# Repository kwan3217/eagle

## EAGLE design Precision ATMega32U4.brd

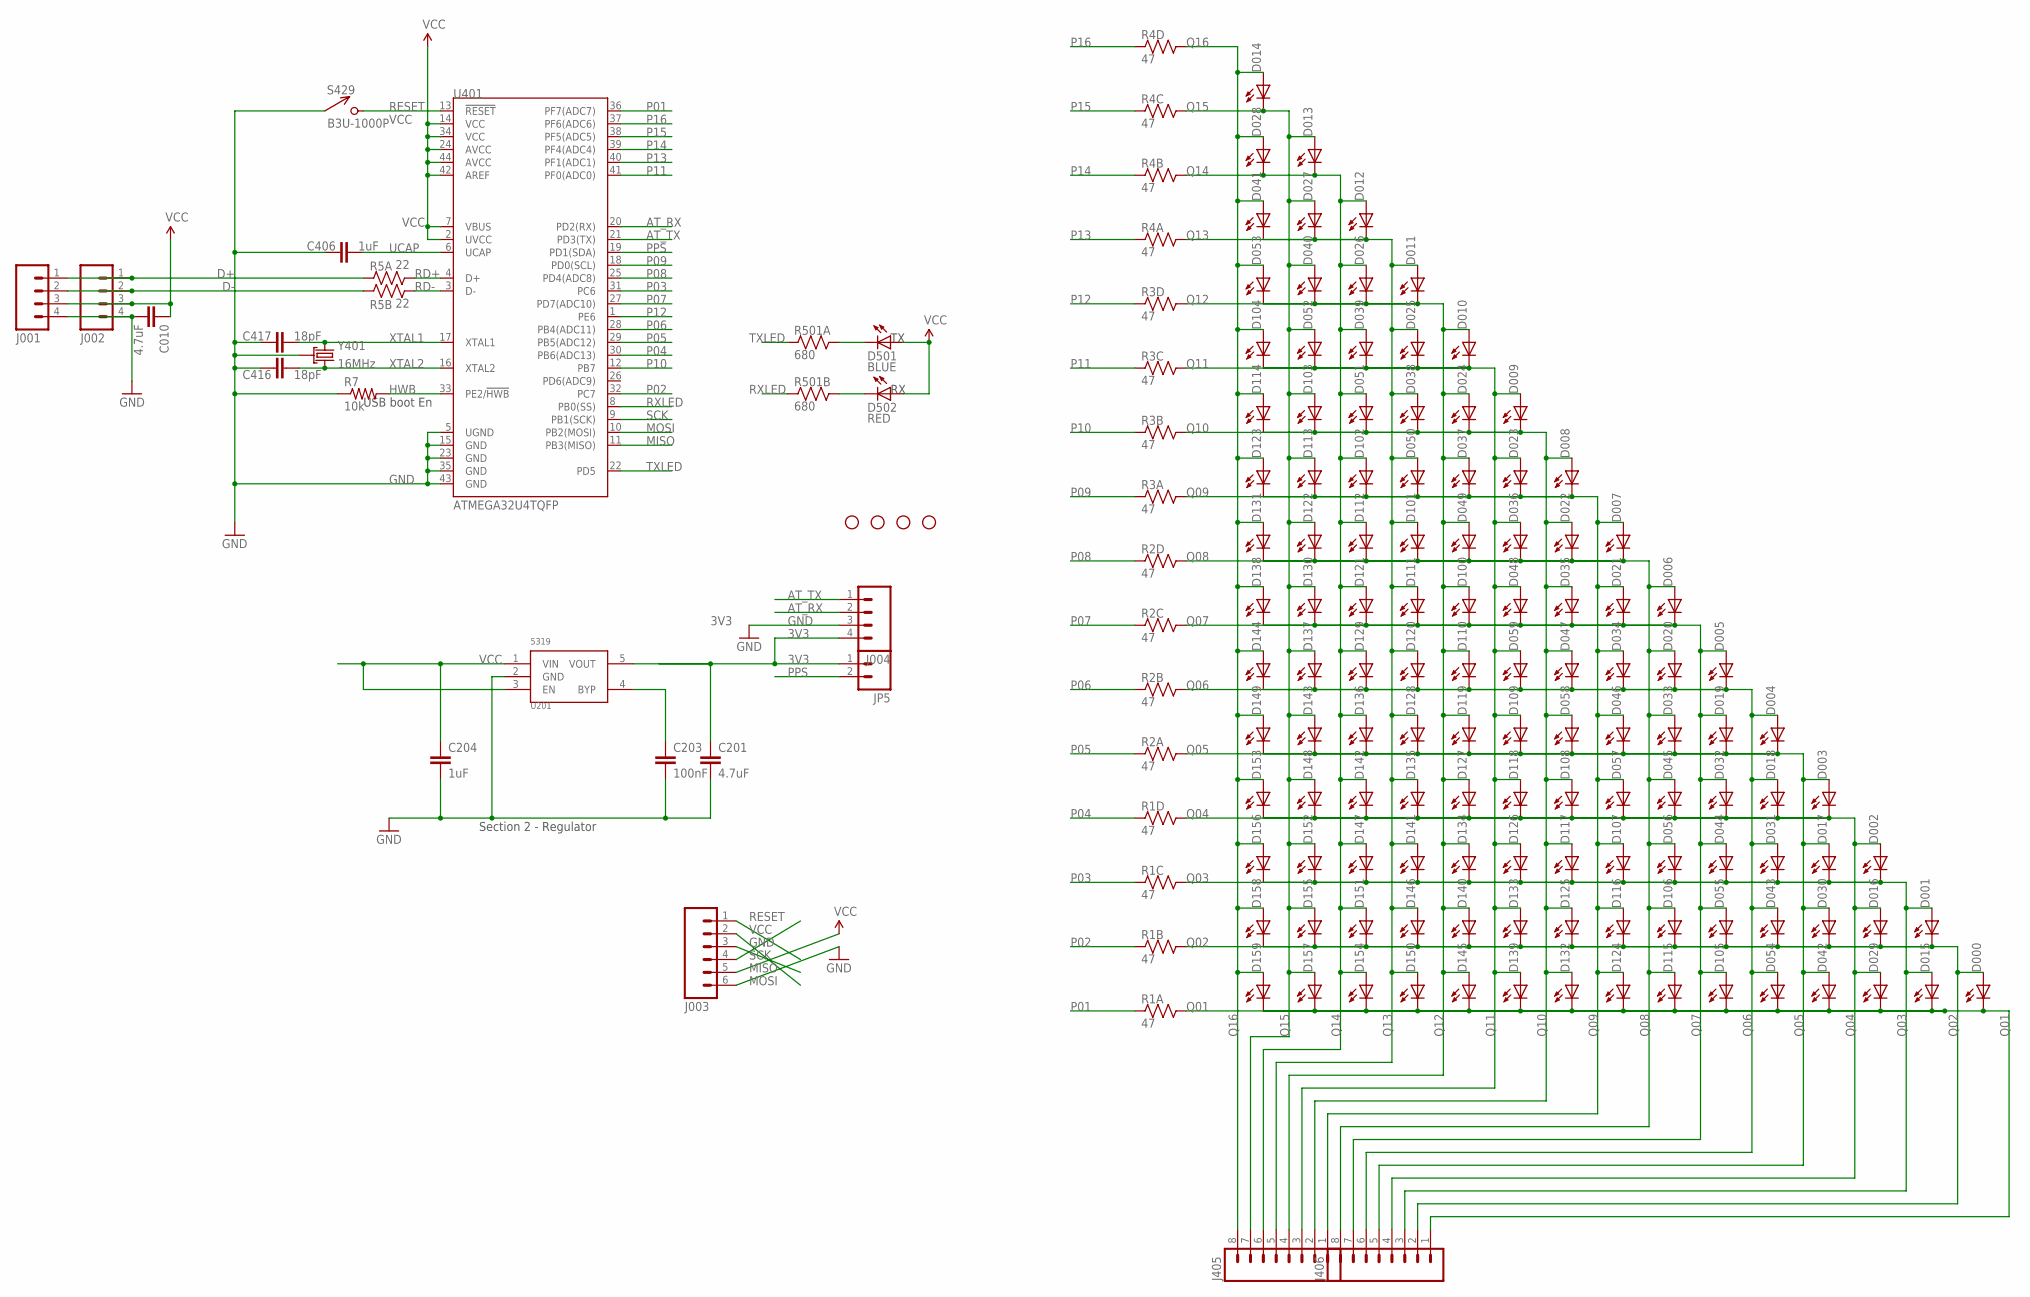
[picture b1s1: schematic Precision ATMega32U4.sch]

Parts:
C010: 4.7uF; 0603-CAP
C201: 4.7uF; 0402-CAP
C203: 100nF; 0402-CAP
C204: 1uF; 0402-CAP
C406: 1uF; 0603-CAP
C416, C417: 18pF; 0603-CAP
D000, D001, D002, D003, D004, D005, D006, D007, D008, D009, D010, D011, D012, D013, D014, D015, D016, D017, D018, D019, D020, D021, D022, D023, D024, D025, D026, D027, D028, D029, D030, D031, D032, D033, D034, D035, D036, D037, D038, D039, D040, D041, D042, D043, D044, D045, D046, D047, D048, D049, D050, D051, D052, D053, D054, D055, D056, D057, D058, D059, D100, D101, D102, D103, D104, D105, D106, D107, D108, D109, D110, D111, D112, D113, D114, D115, D116, D117, D118, D119, D120, D121, D122, D123, D124, D125, D126, D127, D128, D129, D130, D131, D132, D133, D134, D135, D136, D137, D138, D139, D140, D141, D142, D143, D144, D145, D146, D147, D148, D149, D150, D151, D152, D153, D154, D155, D156, D157, D158, D159: HOUR; LED-0603
D501: BLUE; LED-0603
D502: RED; LED-0603
J001, J002, J004: M04PTH; 1X04
J003: M06SIP; 1X06
J405, J406: M081X08; 1X08
JP1, JP2, JP3, JP4: STAND-OFF
JP5: M02PTH; 1X02
R1, R2, R3, R4: 47; CRA04
R5: 22; CRA02
R7: 10k; 0603-RES
R501: 680; CRA02
S429: B3U-1000P
U201: 5319; SOT-23-5
U401: ATMEGA32U4TQFP; SPARKFUN-DIGITALIC_TQFP44
Y401: 16MHz; CRYSTAL_SMD

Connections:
3V3: C201.1, J004.4, JP5.1, U201.5 (VOUT)
AT_RX: J004.2, U401.20 (PD2(RX))
AT_TX: J004.1, U401.21 (PD3(TX))
D+: J001.1, J002.1, R5.1
D-: J001.2, J002.2, R5.2 (1)
GND: C010.2, C201.2, C203.2, C204.2, C406.2, C416.1, C417.1, J001.4, J002.4, J003.6, J004.3, R7.1, S429.P$1 (1), U201.2 (GND), U401.5 (UGND), U401.15 (GND), U401.23 (GND), U401.35 (GND), U401.43 (GND), Y401.2 (GND), Y401.4 (GND)
HWB: R7.2, U401.33 (PE2/!HWB)
MISO: J003.3, U401.11 (PB3(MISO))
MOSI: J003.2, U401.10 (PB2(MOSI))
unnamed: C203.1, U201.4 (BYP)
P01: R1.1, U401.36 (PF7(ADC7))
P02: R1.2 (1), U401.32 (PC7)
P03: R1.3 (1), U401.31 (PC6)
P04: R1.4 (1), U401.30 (PB6(ADC13))
P05: R2.1, U401.29 (PB5(ADC12))
P06: R2.2 (1), U401.28 (PB4(ADC11))
P07: R2.3 (1), U401.27 (PD7(ADC10))
P08: R2.4 (1), U401.25 (PD4(ADC8))
P09: R3.1, U401.18 (PD0(SCL))
P10: R3.2 (1), U401.12 (PB7)
P11: R3.3 (1), U401.41 (PF0(ADC0))
P12: R3.4 (1), U401.1 (PE6)
P13: R4.1, U401.40 (PF1(ADC1))
P14: R4.2 (1), U401.39 (PF4(ADC4))
P15: R4.3 (1), U401.38 (PF5(ADC5))
P16: R4.4 (1), U401.37 (PF6(ADC6))
PPS: JP5.2, U401.19 (PD1(SDA))
Q01: D000.C, D015.C, D029.C, D042.C, D054.C, D105.C, D115.C, D124.C, D132.C, D139.C, D145.C, D150.C, D154.C, D157.C, D159.C, J406.1, R1.8 (2)
Q02: D000.A, D001.C, D016.C, D030.C, D043.C, D055.C, D106.C, D116.C, D125.C, D133.C, D140.C, D146.C, D151.C, D155.C, D158.C, J406.2, R1.7 (2)
Q03: D001.A, D002.C, D015.A, D017.C, D031.C, D044.C, D056.C, D107.C, D117.C, D126.C, D134.C, D141.C, D147.C, D152.C, D156.C, J406.3, R1.6 (2)
Q04: D002.A, D003.C, D016.A, D018.C, D029.A, D032.C, D045.C, D057.C, D108.C, D118.C, D127.C, D135.C, D142.C, D148.C, D153.C, J406.4, R1.5 (2)
Q05: D003.A, D004.C, D017.A, D019.C, D030.A, D033.C, D042.A, D046.C, D058.C, D109.C, D119.C, D128.C, D136.C, D143.C, D149.C, J406.5, R2.8 (2)
Q06: D004.A, D005.C, D018.A, D020.C, D031.A, D034.C, D043.A, D047.C, D054.A, D059.C, D110.C, D120.C, D129.C, D137.C, D144.C, J406.6, R2.7 (2)
Q07: D005.A, D006.C, D019.A, D021.C, D032.A, D035.C, D044.A, D048.C, D055.A, D100.C, D105.A, D111.C, D121.C, D130.C, D138.C, J406.7, R2.6 (2)
Q08: D006.A, D007.C, D020.A, D022.C, D033.A, D036.C, D045.A, D049.C, D056.A, D101.C, D106.A, D112.C, D115.A, D122.C, D131.C, J406.8, R2.5 (2)
Q09: D007.A, D008.C, D021.A, D023.C, D034.A, D037.C, D046.A, D050.C, D057.A, D102.C, D107.A, D113.C, D116.A, D123.C, D124.A, J405.1, R3.8 (2)
Q10: D008.A, D009.C, D022.A, D024.C, D035.A, D038.C, D047.A, D051.C, D058.A, D103.C, D108.A, D114.C, D117.A, D125.A, D132.A, J405.2, R3.7 (2)
Q11: D009.A, D010.C, D023.A, D025.C, D036.A, D039.C, D048.A, D052.C, D059.A, D104.C, D109.A, D118.A, D126.A, D133.A, D139.A, J405.3, R3.6 (2)
Q12: D010.A, D011.C, D024.A, D026.C, D037.A, D040.C, D049.A, D053.C, D100.A, D110.A, D119.A, D127.A, D134.A, D140.A, D145.A, J405.4, R3.5 (2)
Q13: D011.A, D012.C, D025.A, D027.C, D038.A, D041.C, D050.A, D101.A, D111.A, D120.A, D128.A, D135.A, D141.A, D146.A, D150.A, J405.5, R4.8 (2)
Q14: D012.A, D013.C, D026.A, D028.C, D039.A, D051.A, D102.A, D112.A, D121.A, D129.A, D136.A, D142.A, D147.A, D151.A, D154.A, J405.6, R4.7 (2)
Q15: D013.A, D014.C, D027.A, D040.A, D052.A, D103.A, D113.A, D122.A, D130.A, D137.A, D143.A, D148.A, D152.A, D155.A, D157.A, J405.7, R4.6 (2)
Q16: D014.A, D028.A, D041.A, D053.A, D104.A, D114.A, D123.A, D131.A, D138.A, D144.A, D149.A, D153.A, D156.A, D158.A, D159.A, J405.8, R4.5 (2)
RD+: R5.4 (2), U401.4 (D+)
RD-: R5.3 (2), U401.3 (D-)
RESET: J003.4, S429.P$2 (2), U401.13 (!RESET)
RXLED: R501.2 (1), U401.8 (PB0(SS))
RXLED+: D502.C, R501.3 (2)
SCK: J003.1, U401.9 (PB1(SCK))
TXLED: R501.1, U401.22 (PD5)
TXLED+: D501.C, R501.4 (2)
UCAP: C406.1, U401.6 (UCAP)
VCC: C010.1, C204.1, D501.A, D502.A, J001.3, J002.3, J003.5, U201.1 (VIN), U201.3 (EN), U401.2 (UVCC), U401.7 (VBUS), U401.14 (VCC), U401.24 (AVCC), U401.34 (VCC), U401.42 (AREF), U401.44 (AVCC)
XTAL1: C417.2, U401.17 (XTAL1), Y401.1
XTAL2: C416.2, U401.16 (XTAL2), Y401.3 (2)

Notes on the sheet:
USB boot En
Section 2 - Regulator

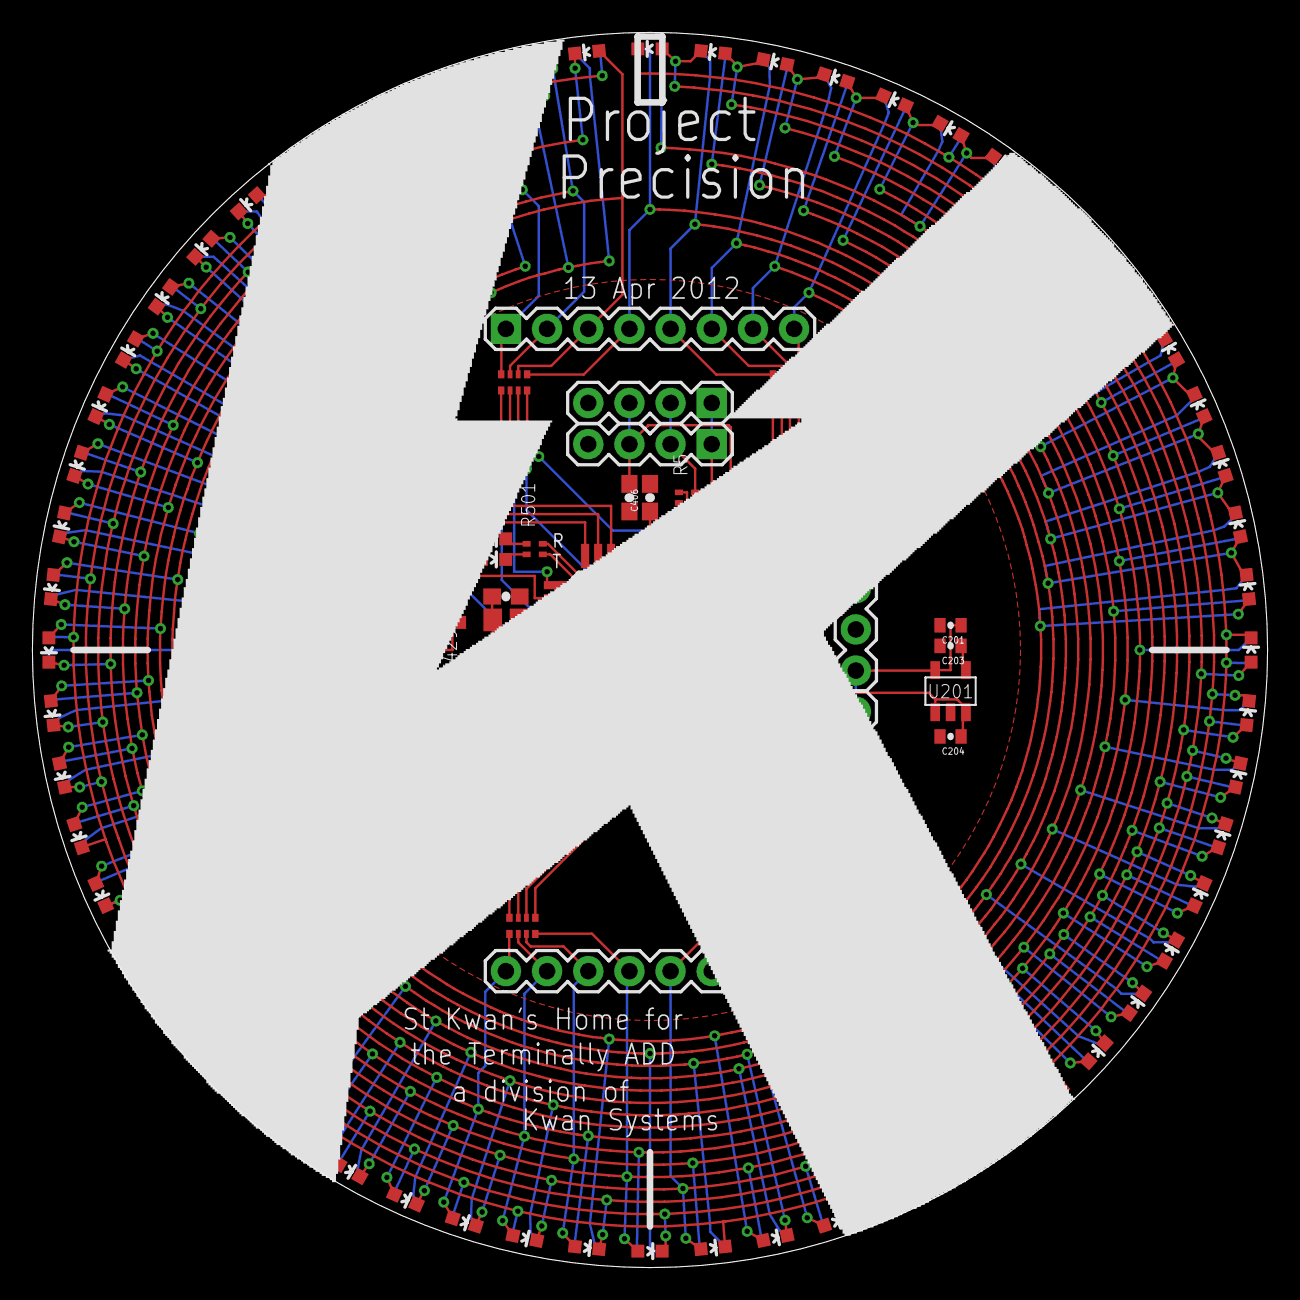
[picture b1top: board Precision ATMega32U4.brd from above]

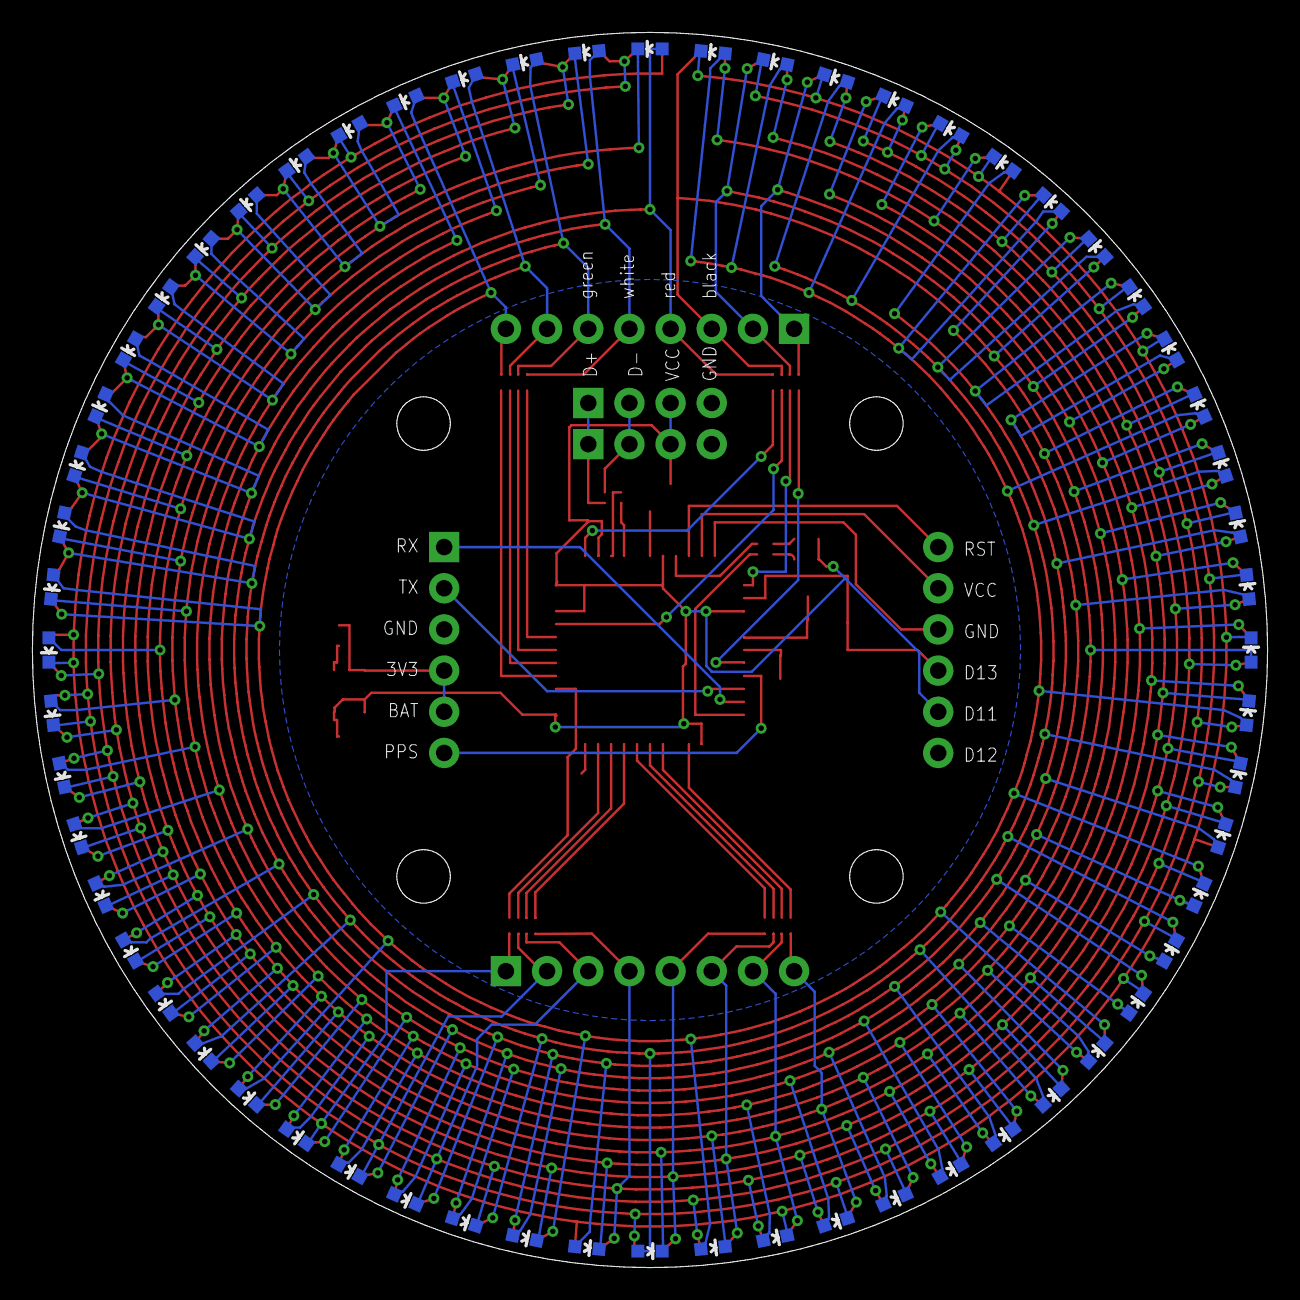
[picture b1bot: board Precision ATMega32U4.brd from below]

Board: 2 copper layers, 76.2 x 76.2 mm, 151 parts (60 on the bottom side), 55 nets.

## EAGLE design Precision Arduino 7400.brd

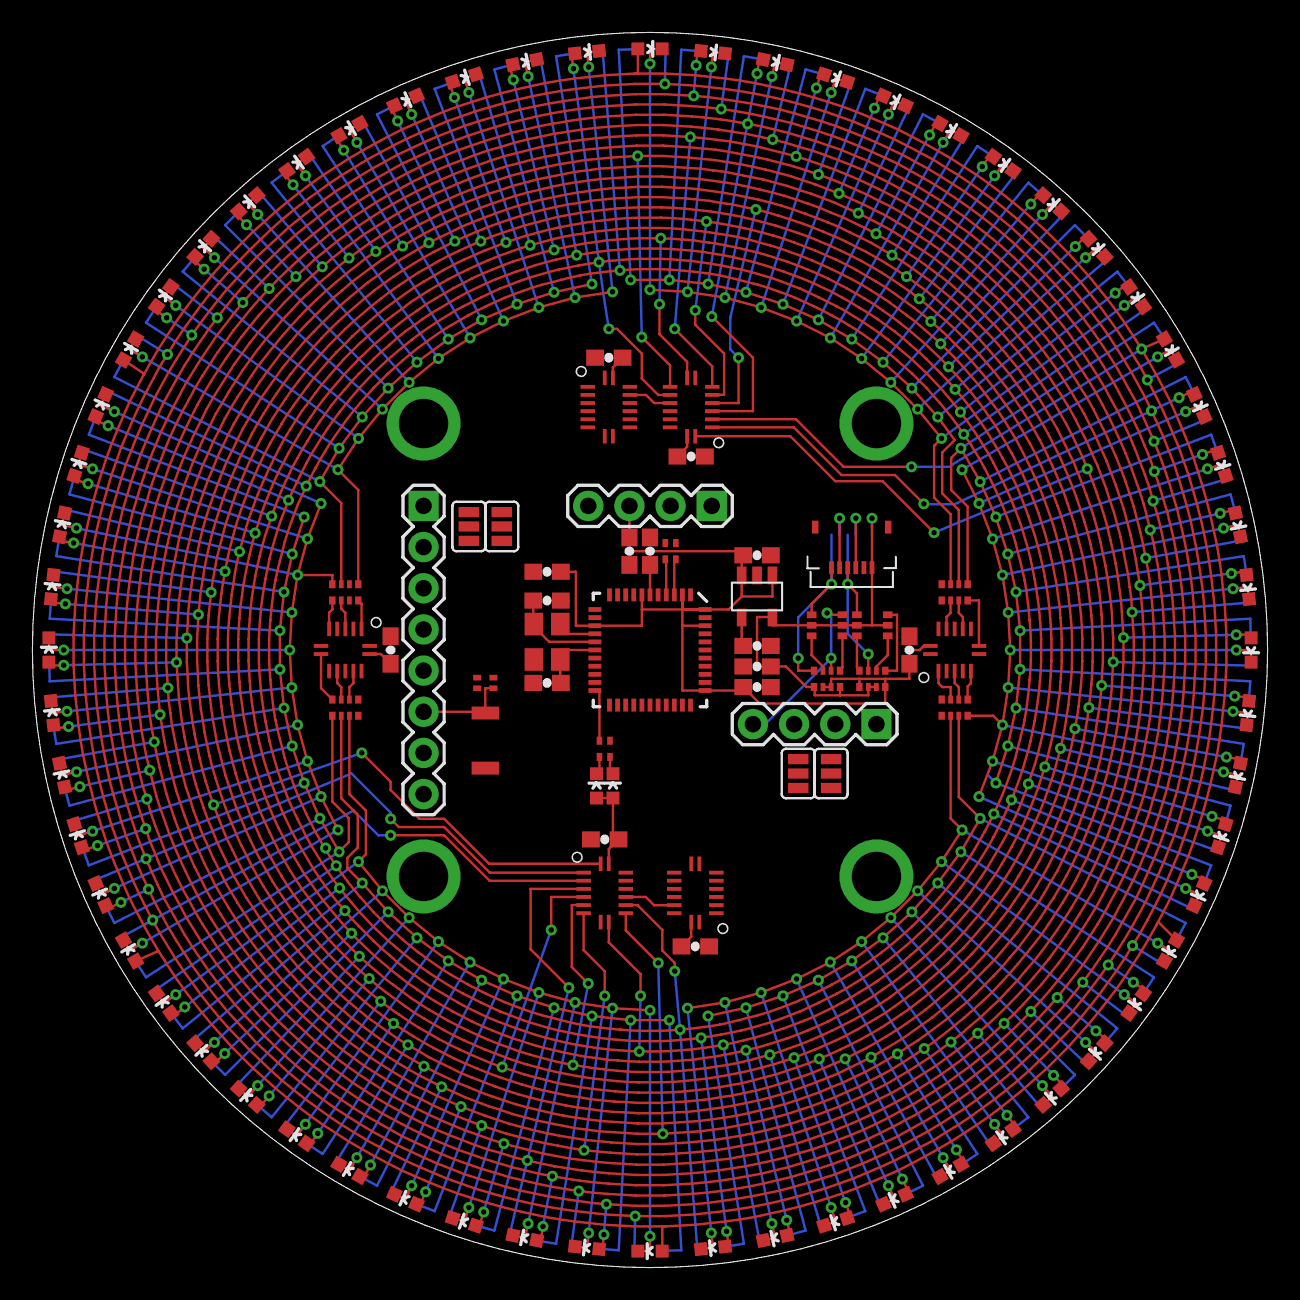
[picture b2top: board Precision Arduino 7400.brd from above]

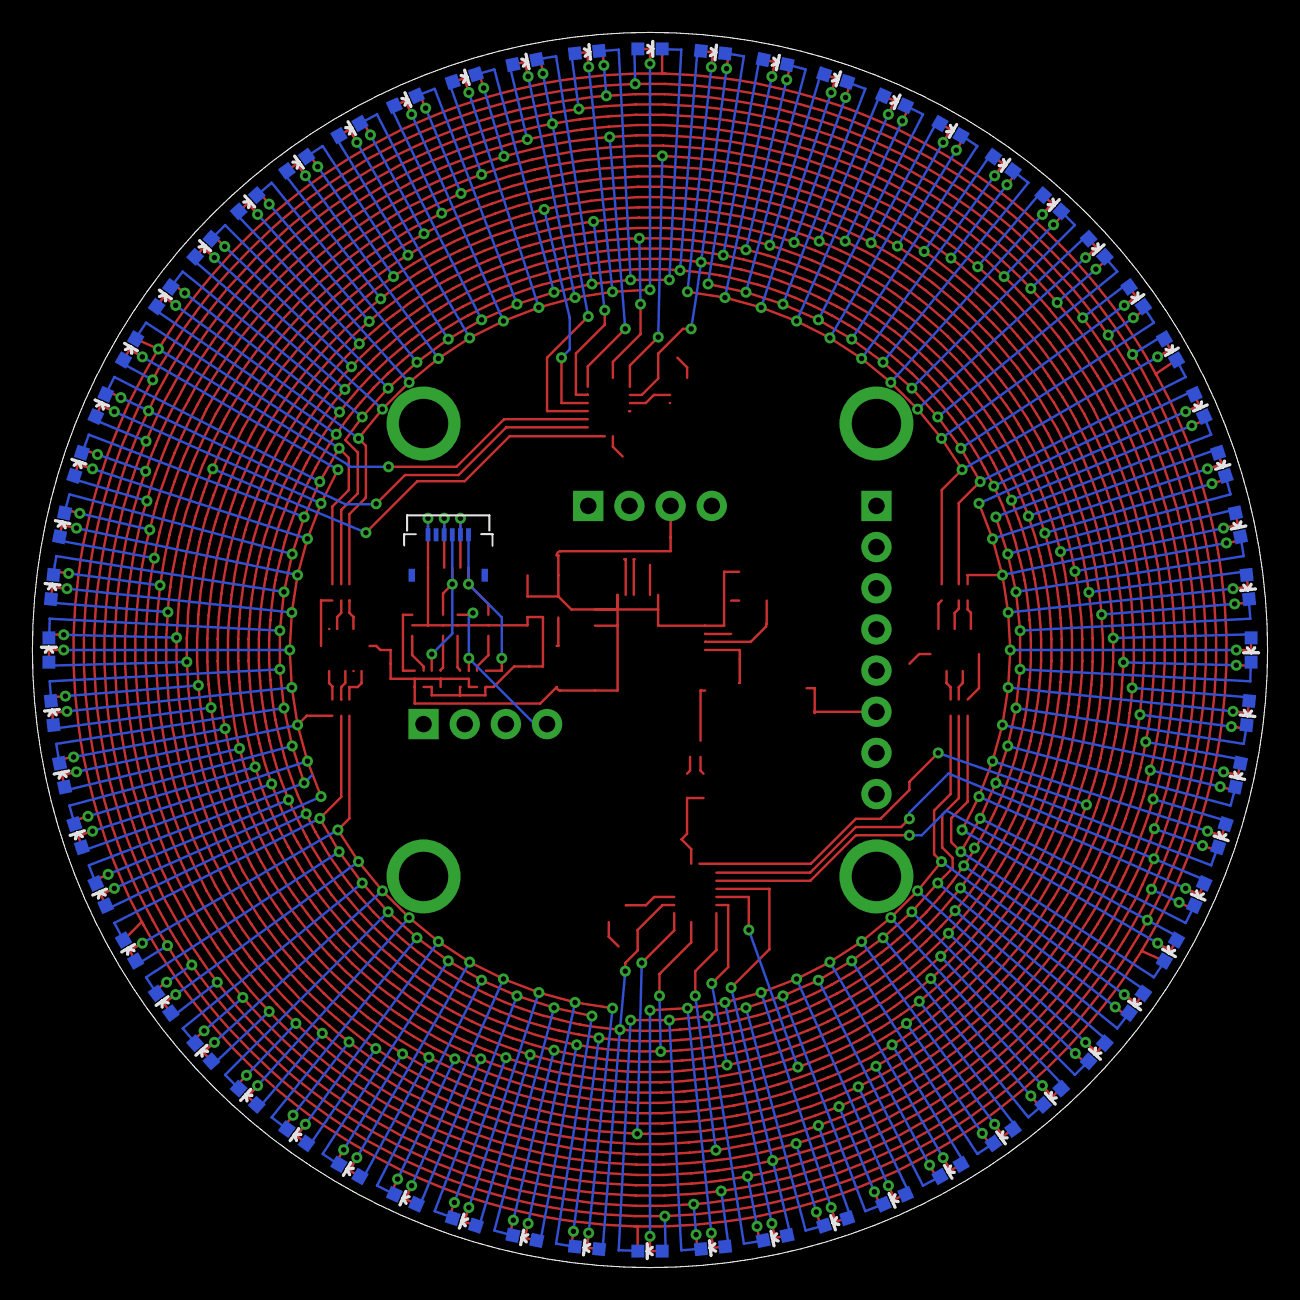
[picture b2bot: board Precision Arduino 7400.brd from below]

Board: 2 copper layers, 76.2 x 76.2 mm, 171 parts (61 on the bottom side), 98 nets.

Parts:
C001, C002, C010, C035, C101, C110, C203, C414, C434: 100nF; 0603-CAP
C004, C201: 4.7uF; 0603-CAP
C204, C406: 1uF; 0603-CAP
C416, C417: 18pF; 0603-CAP
D000, D001, D002, D003, D004, D005, D006, D007, D008, D009, D010, D011, D012, D013, D014, D015, D016, D017, D018, D019, D020, D021, D022, D023, D024, D025, D026, D027, D028, D029, D030, D031, D032, D033, D034, D035, D036, D037, D038, D039, D040, D041, D042, D043, D044, D045, D046, D047, D048, D049, D050, D051, D052, D053, D054, D055, D056, D057, D058, D059, D100, D101, D102, D103, D104, D105, D106, D107, D108, D109, D110, D111, D112, D113, D114, D115, D116, D117, D118, D119, D120, D121, D122, D123, D124, D125, D126, D127, D128, D129, D130, D131, D132, D133, D134, D135, D136, D137, D138, D139, D140, D141, D142, D143, D144, D145, D146, D147, D148, D149, D150, D151, D152, D153, D154, D155, D156, D157, D158, D159, D408: RED; LED-0603
D422: BLUE; LED-0603
JP1, JP2, JP3, JP4: STANDOFF
JP5: 1X04
JPRG: 1X08
JUSB1: 1X04
Q301, Q302: BSS138DW; SOT-363
R5: 22; CRA02
R020, R021, R350, R351: 91; CRA04
R301, R302: 10k; CRA04
R413: 10k; CRA02
R501: 680; CRA02
S0C, S0R, S1C, S1R: SOLDERJUMPER_3WAY; SJ_3
S429: B3U-1000P
U001, U010, U101, U110: 74HC4017; DHVQFN16
U002, U035: 74LVC14A; DHVQFN14
U003, U004: GP-2106
U201: 1.8V; SOT-23-5
U401: ATMEGA32U4QFN2; SPARKFUN-DIGITALIC_QFN-44-NOPAD
Y401: 16MHz; CRYSTAL_SMD

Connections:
1.8V: C201.1, Q301.2, Q301.5, Q302.2, Q302.5, R301.6, R301.7, R302.5, R302.8, U003.VCC, U004.VCC, U201.5
C0: S0C.3, U401.25
C1: S1C.1, U401.27
C2: JPRG.1, S0C.1, U401.28
C3: JP5.2, S1C.3, U401.30
CARRY0: U001.12, U010.14
CARRY1: U101.12, U110.14
CLK0: S0C.COM, U001.14
CLK1: S1C.COM, U101.14
D+: JUSB1.1, R5.2
D-: JUSB1.2, R5.1
GND: C001.1, C002.1, C004.2, C010.1, C035.1, C101.1, C110.1, C201.2, C203.2, C204.2, C406.2, C414.1, C416.1, C417.1, C434.1, JP1.P$1, JP2.P$1, JP3.P$1, JP4.P$1, JPRG.8, JUSB1.4, R413.1, S429.P$1, U001.8, U001.13, U002.7, U003.GND, U004.GND, U010.8, U010.13, U035.7, U101.8, U101.13, U110.8, U110.13, U201.2, U401.5, U401.15, U401.23, U401.35, U401.43, Y401.2, Y401.4
HWB: R413.4, U401.33
MISO: JPRG.5, U401.11
MOSI: JPRG.4, U401.10
unnamed: C203.1, U201.4
ONOFF: Q302.3, R301.1
ONOFF_LO: Q302.4, R301.3, U003.ONOFF, U004.ONOFF
P00X: U002.13, U010.3
P0X0: D000.A, D010.A, D020.A, D030.A, D040.A, D050.A, U001.3
P0X1: D001.A, D011.A, D021.A, D031.A, D041.A, D051.A, U001.2
P0X2: D002.A, D012.A, D022.A, D032.A, D042.A, D052.A, U001.4
P0X3: D003.A, D013.A, D023.A, D033.A, D043.A, D053.A, U001.7
P0X4: D004.A, D014.A, D024.A, D034.A, D044.A, D054.A, U001.10
P0X5: D005.A, D015.A, D025.A, D035.A, D045.A, D055.A, U001.1
P0X6: D006.A, D016.A, D026.A, D036.A, D046.A, D056.A, U001.5
P0X7: D007.A, D017.A, D027.A, D037.A, D047.A, D057.A, U001.6
P0X8: D008.A, D018.A, D028.A, D038.A, D048.A, D058.A, U001.9
P0X9: D009.A, D019.A, D029.A, D039.A, D049.A, D059.A, U001.11
P01X: U002.5, U010.2
P1X0: D100.A, D110.A, D120.A, D130.A, D140.A, D150.A, U101.3
P1X1: D101.A, D111.A, D121.A, D131.A, D141.A, D151.A, U101.2
P1X2: D102.A, D112.A, D122.A, D132.A, D142.A, D152.A, U101.4
P1X3: D103.A, D113.A, D123.A, D133.A, D143.A, D153.A, U101.7
P1X4: D104.A, D114.A, D124.A, D134.A, D144.A, D154.A, U101.10
P1X5: D105.A, D115.A, D125.A, D135.A, D145.A, D155.A, U101.1
P1X6: D106.A, D116.A, D126.A, D136.A, D146.A, D156.A, U101.5
P1X7: D107.A, D117.A, D127.A, D137.A, D147.A, D157.A, U101.6
P1X8: D108.A, D118.A, D128.A, D138.A, D148.A, D158.A, U101.9
P1X9: D109.A, D119.A, D129.A, D139.A, D149.A, D159.A, U101.11
P02X: U002.1, U010.4
P03X: U010.7, U035.13
P04X: U010.10, U035.5
P05X: U010.1, U035.1
P10X: U002.11, U110.3
P11X: U002.9, U110.2
P12X: U002.3, U110.4
P13X: U035.11, U110.7
P14X: U035.9, U110.10
P15X: U035.3, U110.1
PPS: Q302.6, R301.4, U401.19
PPS_LO: Q302.1, R301.2, U003.1PPS, U004.1PPS
Q00X: R021.2, U002.12
Q01X: R020.1, U002.6
Q02X: R020.3, U002.2
Q03X: R350.2, U035.12
Q04X: R351.1, U035.6
Q05X: R351.4, U035.2
Q10X: R021.3, U002.10
Q11X: R021.4, U002.8
Q12X: R020.2, U002.4
Q13X: R350.3, U035.10
Q14X: R350.4, U035.8
Q15X: R351.2, U035.4
QQ00X: D000.C, D001.C, D002.C, D003.C, D004.C, D005.C, D006.C, D007.C, D008.C, D009.C, R021.7
QQ01X: D010.C, D011.C, D012.C, D013.C, D014.C, D015.C, D016.C, D017.C, D018.C, D019.C, R020.8
QQ02X: D020.C, D021.C, D022.C, D023.C, D024.C, D025.C, D026.C, D027.C, D028.C, D029.C, R020.6
QQ03X: D030.C, D031.C, D032.C, D033.C, D034.C, D035.C, D036.C, D037.C, D038.C, D039.C, R350.7
QQ04X: D040.C, D041.C, D042.C, D043.C, D044.C, D045.C, D046.C, D047.C, D048.C, D049.C, R351.8
QQ05X: D050.C, D051.C, D052.C, D053.C, D054.C, D055.C, D056.C, D057.C, D058.C, D059.C, R351.5
QQ10X: D100.C, D101.C, D102.C, D103.C, D104.C, D105.C, D106.C, D107.C, D108.C, D109.C, R021.6
QQ11X: D110.C, D111.C, D112.C, D113.C, D114.C, D115.C, D116.C, D117.C, D118.C, D119.C, R021.5
QQ12X: D120.C, D121.C, D122.C, D123.C, D124.C, D125.C, D126.C, D127.C, D128.C, D129.C, R020.7
QQ13X: D130.C, D131.C, D132.C, D133.C, D134.C, D135.C, D136.C, D137.C, D138.C, D139.C, R350.6
QQ14X: D140.C, D141.C, D142.C, D143.C, D144.C, D145.C, D146.C, D147.C, D148.C, D149.C, R350.5
QQ15X: D150.C, D151.C, D152.C, D153.C, D154.C, D155.C, D156.C, D157.C, D158.C, D159.C, R351.7
R0: S0R.3, U401.18
R1: S1R.3, U401.31
R2: JPRG.2, S0R.1, U401.1
R3: JP5.1, S1R.1, U401.29
RD+: R5.3, U401.4
RD-: R5.4, U401.3
RESET: JPRG.6, R413.3, S429.P$2, U401.13
RST0: S0R.COM, U001.15, U010.15
RST1: S1R.COM, U101.15, U110.15
RX: JP5.4, Q301.6, R302.2, U401.20
RXLED: R501.1, U401.8
RXLED+: D408.C, R501.4
RX_LO: Q301.4, R302.1, U003.RX, U004.RX
SCK: JPRG.3, U401.9
TX: JP5.3, Q301.3, R302.3, U401.21
TXLED: R501.2, U401.22
TXLED+: D422.C, R501.3
TX_LO: Q301.1, R302.4, U003.TX, U004.TX
UCAP: C406.1, U401.6
VCC: C001.2, C002.2, C004.1, C010.2, C035.2, C101.2, C110.2, C204.1, C414.2, C434.2, D408.A, D422.A, JPRG.7, JUSB1.3, R301.5, R301.8, R302.6, R302.7, R413.2, U001.16, U002.14, U010.16, U035.14, U101.16, U110.16, U201.1, U201.3, U401.2, U401.7, U401.14, U401.24, U401.34, U401.42, U401.44
XTAL1: C417.2, U401.17, Y401.1
XTAL2: C416.2, U401.16, Y401.3

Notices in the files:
parts and their libraries:
SparkFun-DigitalIC: Licensing: CC v3.0 Share-Alike You are welcome to use this library for commercial purposes.
